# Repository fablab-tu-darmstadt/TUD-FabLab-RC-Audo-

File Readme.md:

Fablab AUDO
Remote Controlled via Internet 
Video Enabled
Modellcar 

ssh +X
mplayer tv:// -tv driver=v4l2:width=320:height=176:device=/dev/video0:fps=30:outfmt=yuy2

Pins:

PB10: MIEZ Servo PWM
PB4: Steering PWM
PB5: Motor PWM
PB0: Flyer PWM
PB1: Gummi PWM

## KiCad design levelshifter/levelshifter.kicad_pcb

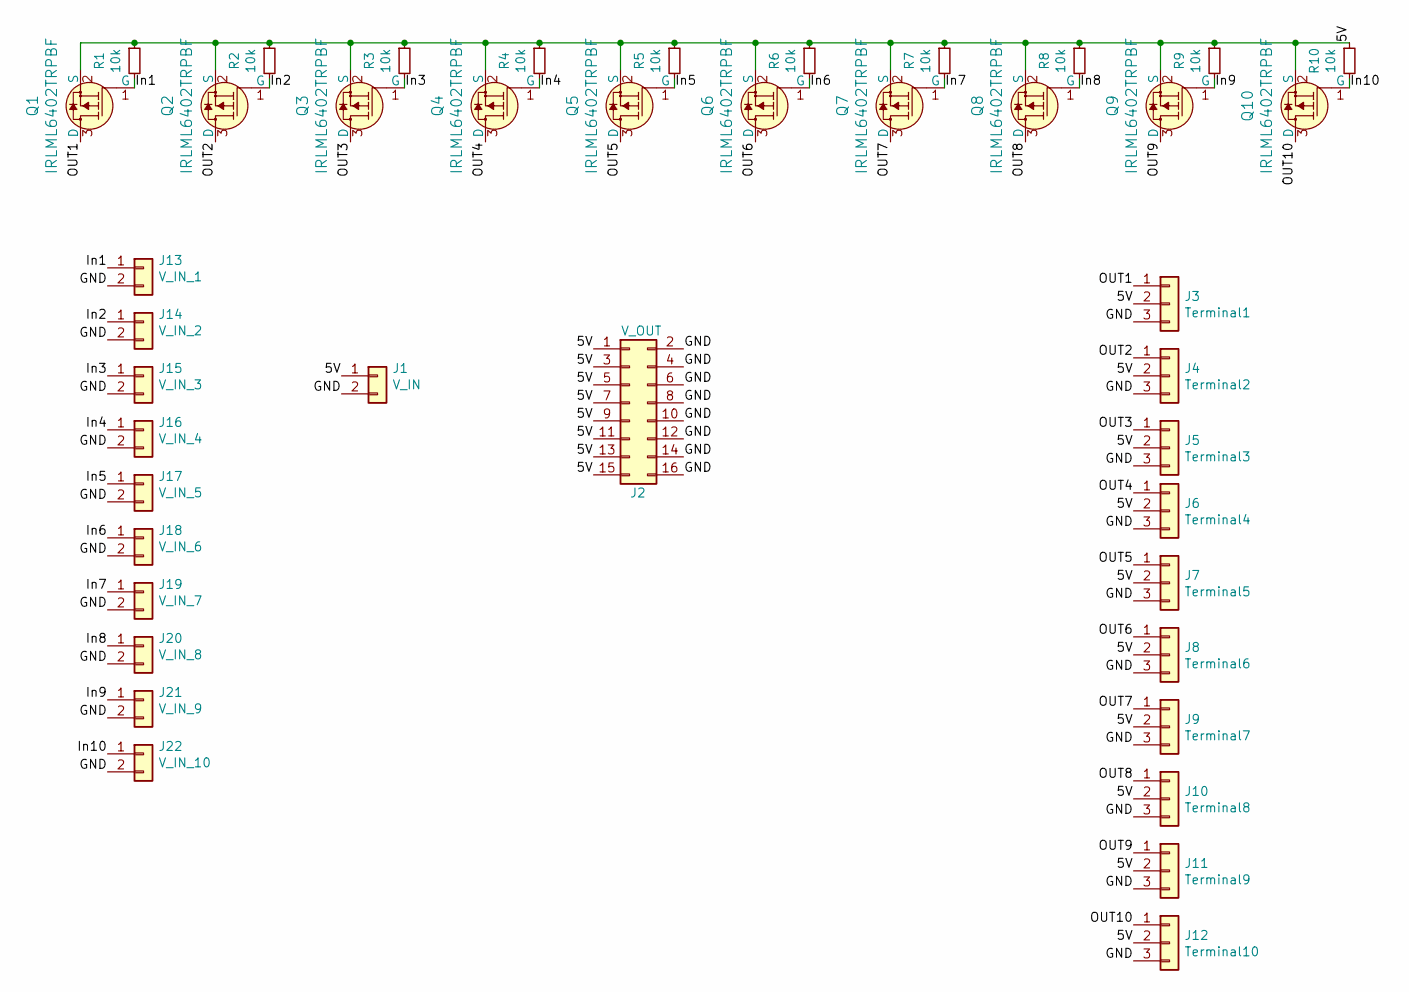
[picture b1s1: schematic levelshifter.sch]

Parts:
J1: V_IN; PinHeader_1x02_P2.54mm_Vertical
J2: V_OUT; PinHeader_2x08_P2.54mm_Vertical
J3: Terminal1; PinHeader_1x03_P2.54mm_Vertical
J4: Terminal2; PinHeader_1x03_P2.54mm_Vertical
J5: Terminal3; PinHeader_1x03_P2.54mm_Vertical
J6: Terminal4; PinHeader_1x03_P2.54mm_Vertical
J7: Terminal5; PinHeader_1x03_P2.54mm_Vertical
J8: Terminal6; PinHeader_1x03_P2.54mm_Vertical
J9: Terminal7; PinHeader_1x03_P2.54mm_Vertical
J10: Terminal8; PinHeader_1x03_P2.54mm_Vertical
J11: Terminal9; PinHeader_1x03_P2.54mm_Vertical
J12: Terminal10; PinHeader_1x03_P2.54mm_Vertical
J13: V_IN_1; PinHeader_1x02_P2.54mm_Vertical
J14: V_IN_2; PinHeader_1x02_P2.54mm_Vertical
J15: V_IN_3; PinHeader_1x02_P2.54mm_Vertical
J16: V_IN_4; PinHeader_1x02_P2.54mm_Vertical
J17: V_IN_5; PinHeader_1x02_P2.54mm_Vertical
J18: V_IN_6; PinHeader_1x02_P2.54mm_Vertical
J19: V_IN_7; PinHeader_1x02_P2.54mm_Vertical
J20: V_IN_8; PinHeader_1x02_P2.54mm_Vertical
J21: V_IN_9; PinHeader_1x02_P2.54mm_Vertical
J22: V_IN_10; PinHeader_1x02_P2.54mm_Vertical
Q1, Q2, Q3, Q4, Q5, Q6, Q7, Q8, Q9, Q10: IRLML6402TRPBF; SOT-23_Handsoldering; MPN IRLML6402TRPBF; Digi-Key_PN IRLML6402PBFCT-ND
R1, R2, R3, R4, R5, R6, R7, R8, R9, R10: 10k; R_0603_1608Metric_Pad1.05x0.95mm_HandSolder

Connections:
/5V: J1.1, J2.1, J2.3, J2.5, J2.7, J2.9, J2.11, J2.13, J2.15, J3.2, J4.2, J5.2, J6.2, J7.2, J8.2, J9.2, J10.2, J11.2, J12.2, Q1.2 (S), Q2.2 (S), Q3.2 (S), Q4.2 (S), Q5.2 (S), Q6.2 (S), Q7.2 (S), Q8.2 (S), Q9.2 (S), Q10.2 (S), R1.1, R2.1, R3.1, R4.1, R5.1, R6.1, R7.1, R8.1, R9.1, R10.1
/GND: J1.2, J2.2, J2.4, J2.6, J2.8, J2.10, J2.12, J2.14, J2.16, J3.3, J4.3, J5.3, J6.3, J7.3, J8.3, J9.3, J10.3, J11.3, J12.3, J13.2, J14.2, J15.2, J16.2, J17.2, J18.2, J19.2, J20.2, J21.2, J22.2
/In1: J13.1, Q1.1 (G), R1.2
/In2: J14.1, Q2.1 (G), R2.2
/In3: J15.1, Q3.1 (G), R3.2
/In4: J16.1, Q4.1 (G), R4.2
/In5: J17.1, Q5.1 (G), R5.2
/In6: J18.1, Q6.1 (G), R6.2
/In7: J19.1, Q7.1 (G), R7.2
/In8: J20.1, Q8.1 (G), R8.2
/In9: J21.1, Q9.1 (G), R9.2
/In10: J22.1, Q10.1 (G), R10.2
/OUT1: J3.1, Q1.3 (D)
/OUT2: J4.1, Q2.3 (D)
/OUT3: J5.1, Q3.3 (D)
/OUT4: J6.1, Q4.3 (D)
/OUT5: J7.1, Q5.3 (D)
/OUT6: J8.1, Q6.3 (D)
/OUT7: J9.1, Q7.3 (D)
/OUT8: J10.1, Q8.3 (D)
/OUT9: J11.1, Q9.3 (D)
/OUT10: J12.1, Q10.3 (D)

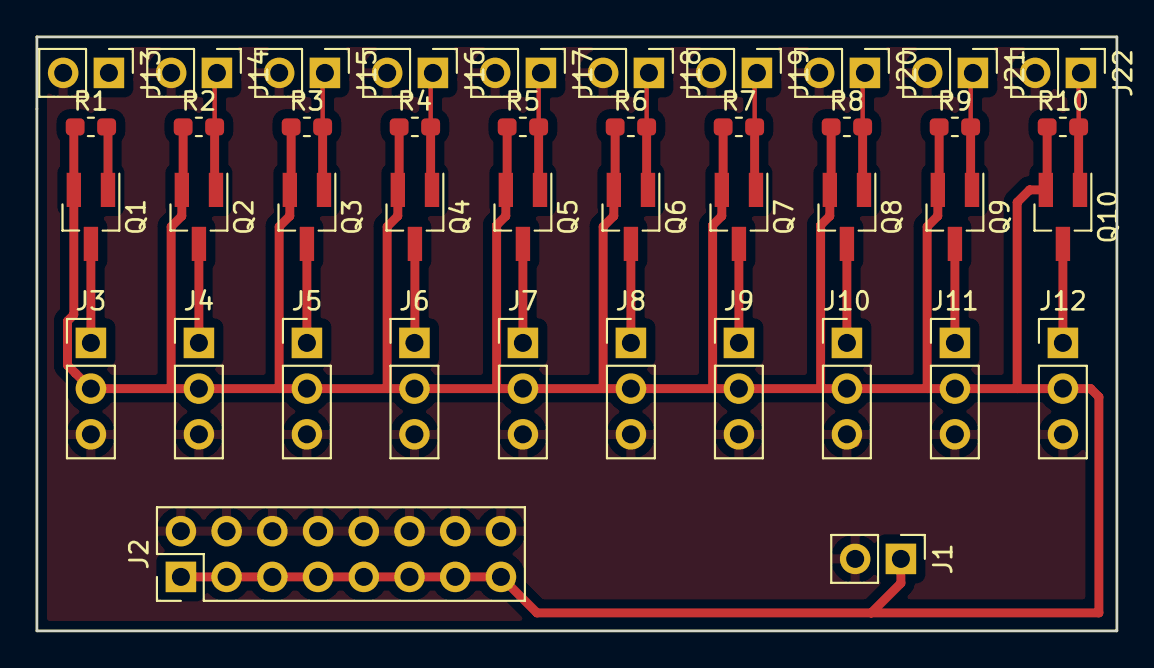
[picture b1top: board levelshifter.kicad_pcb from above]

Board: 2 copper layers, 60.0 x 33.0 mm, 42 parts (0 on the bottom side), 22 nets.

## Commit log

2019-10-10 The world is watching you
2019-10-10 Started with STM32 Nucleo
2019-10-10 Setup communication with STM32
2019-10-11 Motor and Steering Control, basic python script for serial com
2019-10-14 Started telegram bot, not yet reliable
2019-10-18 Wrote Python UDP Server and Clients
2019-10-18 Continued Remote Controll
2019-10-21 Created Plattform
2019-11-07 Many Things and more stuff happened, wow
2019-11-15 Finished Ladeflaeche
2019-11-15 cleanup
2019-11-15 added tests scripts
2019-11-15 fixed tabs and such
2019-11-15 removed old file
2019-11-15 added gitignore
2019-11-15 removed some junk files
2019-11-15 added jpg and mjpg to gitignore
2019-11-15 removed junk file
2019-11-15 added sender and recorder
2019-11-15 wrote sender to output to stdout as raw bytes, recorder records
2019-11-22 added sigint handler
2019-11-22 sender is joined on sigint
2019-11-22 formatting
2019-11-22 sigint clears sender queue
2019-11-22 added wait in recorder
2019-11-22 bind port
2019-11-22 fixed print
2019-11-22 listen for laptop connection on server
2019-11-22 changed stream to dgram
2019-11-22 string to bytes
2019-11-23 something
2019-11-23 Many things
2019-11-23 server update
2019-11-23 fixed audo.py
2019-11-23 set fps to 15
2019-11-23 added socket and print out size of input
2019-11-23 fixed audo.py again hopefully
2019-11-23 pi sends stuff to server
2019-11-23 added sleep in recorder, added logging in server
2019-11-23 Implemented MIEZgit add *!
2019-11-24 Pinout
2019-11-24 Created Blinds
2019-11-25 implemented movement directives
2019-11-25 audo.py progress and first real world tests
2019-11-25 good bye levelshifter
2022-05-02 added SX1278 lib
2022-05-02 cubemx code gen...
